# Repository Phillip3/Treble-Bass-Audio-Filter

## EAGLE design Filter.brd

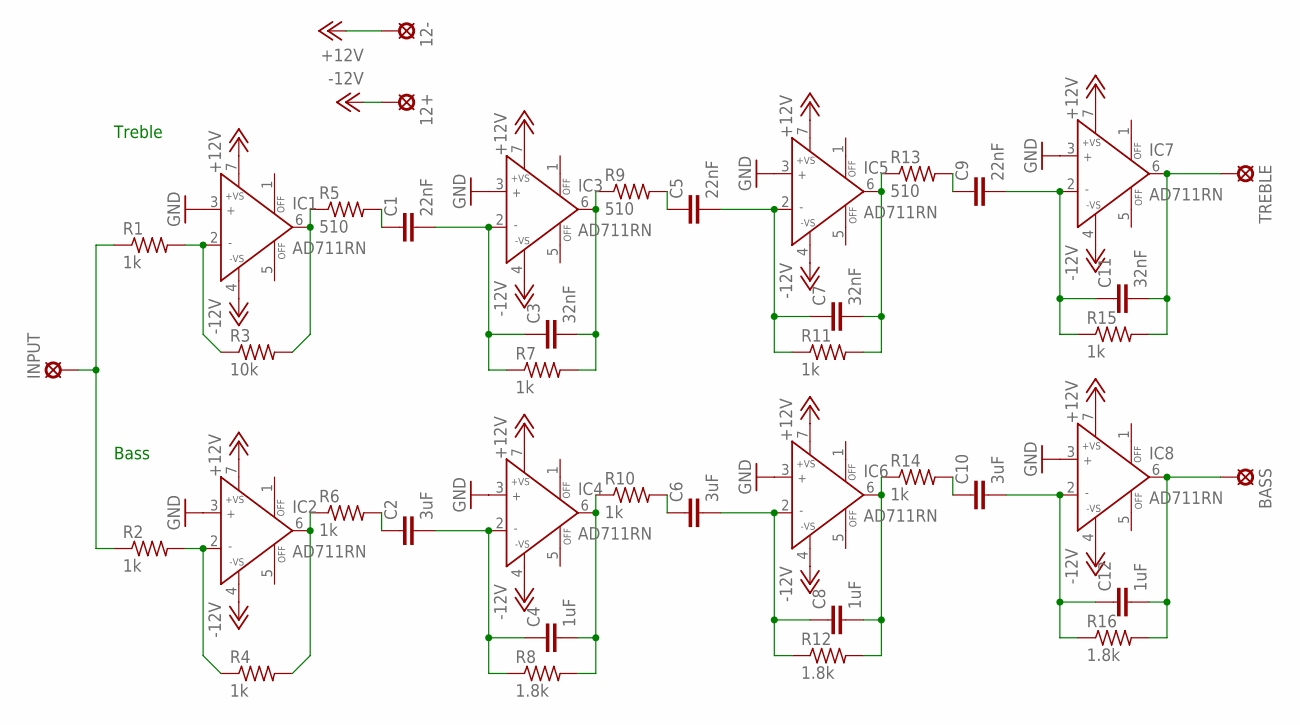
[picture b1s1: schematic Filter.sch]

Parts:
12+, 12-: MCS10B
BASS: MCS10B
C1, C5, C9: 22nF; C0805; MPN UA741CPE4
C2, C6, C10: 3uF; C0805; MPN TMCP1C335KTRF
C3, C7, C11: 32nF; C0805
C4, C8, C12: 1uF; C0805; MPN 6TPU33MSK
IC1, IC2, IC3, IC4, IC5, IC6, IC7, IC8: AD711RN; SO8; MPN UA741CP
INPUT: MCS10B
R1, R2, R4, R6, R7, R10, R11, R14, R15: 1k; R0603; MPN ERJ-3EKF1001V
R3: 10k; R0805; MPN MC0603B104K500CT
R5, R9, R13: 510; R0805; MPN ERA-6AEB511V
R8, R12, R16: 1.8k; R0805; MPN ERA-6AEB182V
TREBLE: MCS10B

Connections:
+12V: 12-.MP, IC1.7 (+VS), IC2.7 (+VS), IC3.7 (+VS), IC4.7 (+VS), IC5.7 (+VS), IC6.7 (+VS), IC7.7 (+VS), IC8.7 (+VS)
-12V: 12+.MP, IC1.4 (-VS), IC2.4 (-VS), IC3.4 (-VS), IC4.4 (-VS), IC5.4 (-VS), IC6.4 (-VS), IC7.4 (-VS), IC8.4 (-VS)
GND: IC1.3 (IN+), IC2.3 (IN+), IC3.3 (IN+), IC4.3 (IN+), IC5.3 (IN+), IC6.3 (IN+), IC7.3 (IN+), IC8.3 (IN+)
unnamed: IC1.2 (IN-), R1.2, R3.1
unnamed: IC1.6 (OUT), R3.2, R5.1
unnamed: C1.1, R5.2
unnamed: C1.2, C3.1, IC3.2 (IN-), R7.1
unnamed: C3.2, IC3.6 (OUT), R7.2, R9.1
unnamed: C5.2, C7.1, IC5.2 (IN-), R11.1
unnamed: C5.1, R9.2
unnamed: C7.2, IC5.6 (OUT), R11.2, R13.1
unnamed: C9.1, R13.2
unnamed: C9.2, C11.1, IC7.2 (IN-), R15.1
unnamed: C11.2, IC7.6 (OUT), R15.2, TREBLE.MP
unnamed: IC2.2 (IN-), R2.2, R4.1
unnamed: IC2.6 (OUT), R4.2, R6.1
unnamed: C2.1, R6.2
unnamed: C2.2, C4.1, IC4.2 (IN-), R8.1
unnamed: C4.2, IC4.6 (OUT), R8.2, R10.1
unnamed: C6.1, R10.2
unnamed: C6.2, C8.1, IC6.2 (IN-), R12.1
unnamed: C8.2, IC6.6 (OUT), R12.2, R14.1
unnamed: C10.1, R14.2
unnamed: C10.2, C12.1, IC8.2 (IN-), R16.1
unnamed: BASS.MP, C12.2, IC8.6 (OUT), R16.2
unnamed: INPUT.MP, R1.1, R2.1

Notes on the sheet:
Treble
Bass

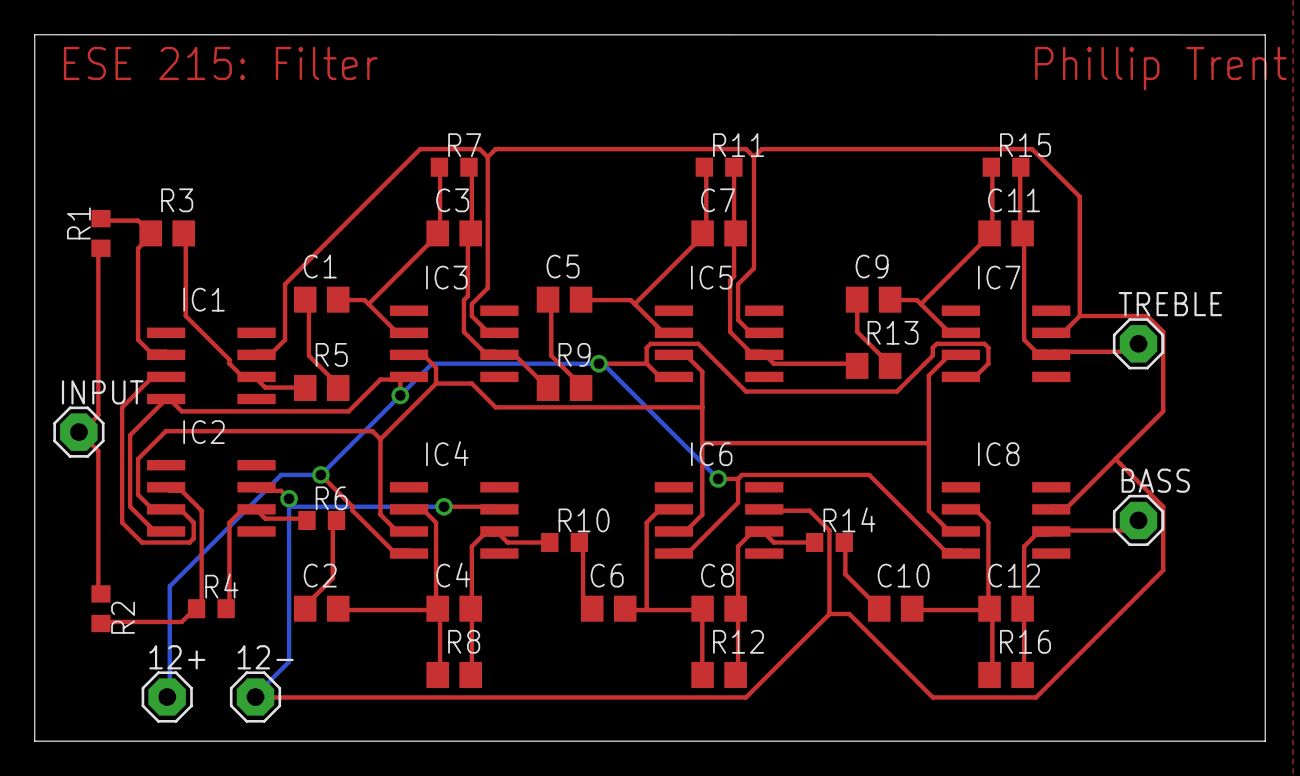
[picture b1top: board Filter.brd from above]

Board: 2 copper layers, 70.8 x 40.6 mm, 41 parts (0 on the bottom side), 26 nets.

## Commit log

2015-12-31 Initial Commit
    Everything should be done with the Schematic and Board design.
2015-12-31 Updates
    Updates after save and quit; nothing major.
